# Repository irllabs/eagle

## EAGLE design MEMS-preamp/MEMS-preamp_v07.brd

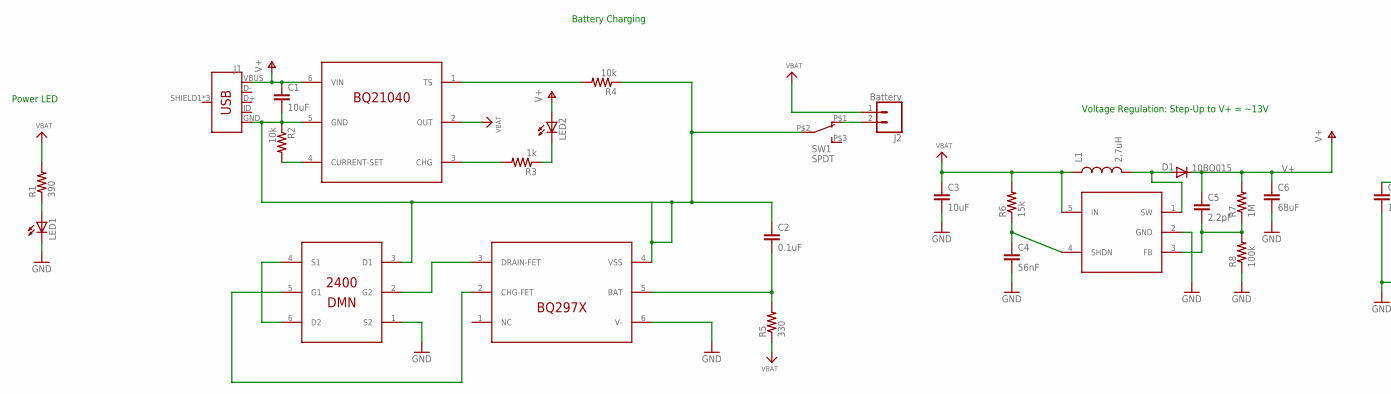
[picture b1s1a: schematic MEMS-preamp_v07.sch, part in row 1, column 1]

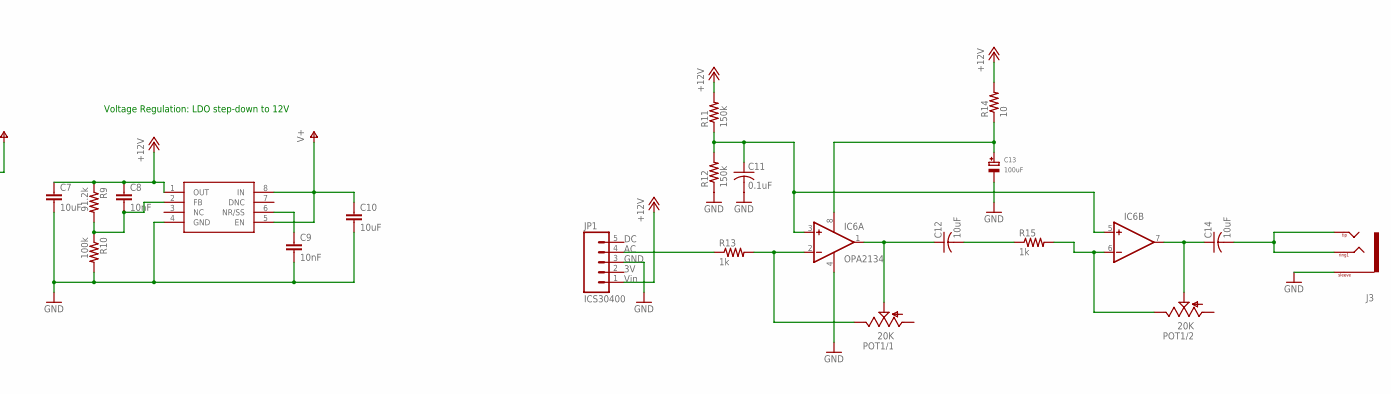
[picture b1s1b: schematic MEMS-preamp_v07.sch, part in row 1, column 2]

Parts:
C1, C3, C7, C10: 10uF; C0603
C2: 0.1uF; C0603
C4: 56nF; C0603
C5: 2.2pF; C0603
C6: 68uF; C1206
C8, C9: 10nF; C0603
C11: 0.1uF; C0805
C12, C14: 10uF; C0805
C13: 100uF; EIA3216-18/A-R
D1: 10BQ015; SMA-DIODE
IC1: DMN2400; SOT-563
IC2: BQ21040; SOT23-6
IC3: BQ297X; WSON-6
IC4: SC4503; SOT23-5
IC5: TPS7A49; MSOP-8
IC6: OPA2134; SO08
J1: USB_MICRO-BREDUCED_PASTE; USB-B-MICRO-SMD_RED_PASTE
J2: Battery; 1X02_LOCK
J3: TRS-1/8"-3.5MM; TRS_SJ-3524-SMT
JP1: ICS30400; 1X05_LOCK
L1: 2.7uH; CR54-KIT
LED1, LED2: LED3MM
POT1: 20K; PTV112
R1: 390; R0603
R2, R4: 10k; R0603
R3, R13, R15: 1k; R0603
R5: 330; R0603
R6: 15k; R0603
R7: 1M; R0603
R8, R10: 100k; R0603
R9: 91.2k; R0603
R11, R12: 150k; R0603
R14: 10; R0603
SW1: SPDT; SWITCH_SPDT_CL-SB-12B

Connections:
+12V: C7.1, C8.1, IC5.1 (OUT), JP1.1, R9.1, R11.2, R14.2
GND: C3.2, C4.2, C6.2, C7.2, C9.2, C10.2, C11.2, C13.-, IC1.1 (S2), IC3.6 (V-), IC5.4 (GND), IC6.4 (V-), J3.1 (SLEEVE), JP1.3, LED1.K (C), R8.1, R10.2, R12.1
GND2: C1.2, C2.1, IC1.3 (D1), IC2.5 (GND), IC3.4 (VSS), J1.GND, R2.1, R4.1, SW1.P$2 (2)
GROU[: IC6.6 (-IN), POT1.2.3 (E), R15.2
unnamed: C13.+, IC6.8 (V+), R14.1
unnamed: LED1.A, R1.1
unnamed: JP1.4, R13.1
unnamed: C12.2, R15.1
unnamed: IC6.2 (-IN), POT1.1.3 (E), R13.2
unnamed: J2.2, SW1.P$1 (1)
unnamed: C14.2, J3.2 (TIP), J3.3 (RING1), J3.4 (TIP)
unnamed: C11.1, IC6.3 (+IN), IC6.5 (+IN), R11.1, R12.2
unnamed: C12.1, IC6.1 (OUT), POT1.1.2 (S)
unnamed: C14.1, IC6.7 (OUT), POT1.2.2 (S)
unnamed: LED2.K (C), R3.1
unnamed: D1.A, IC4.1 (SW), L1.P$2 (2)
unnamed: C4.1, IC4.4 (SHDN), R6.1
unnamed: C5.2, IC4.3 (FB), R7.1, R8.2
unnamed: IC2.3 (CHG), R3.2
unnamed: IC2.1 (TS), R4.2
unnamed: IC2.4 (CURRENT-SET), R2.2
unnamed: C2.2, IC3.5 (BAT), R5.2
unnamed: IC1.4 (S1), IC1.6 (D2)
unnamed: IC1.5 (G1), IC3.2 (CHG-FET)
unnamed: IC1.2 (G2), IC3.3 (DRAIN-FET)
unnamed: C8.2, IC5.2 (FB), R9.2, R10.1
unnamed: C9.1, IC5.6 (NR/SS)
V+: C1.1, C5.1, C6.1, C10.1, D1.C, IC2.6 (VIN), IC5.5 (EN), IC5.8 (IN), J1.VBUS, LED2.A, R7.2
VBAT: C3.1, IC2.2 (OUT), IC4.5 (IN), J2.1, L1.P$1 (1), R1.2, R5.1, R6.2

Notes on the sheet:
Voltage Regulation: Step-Up to V+ = ~13V
Power LED
Voltage Regulation: LDO step-down to 12V
Battery Charging

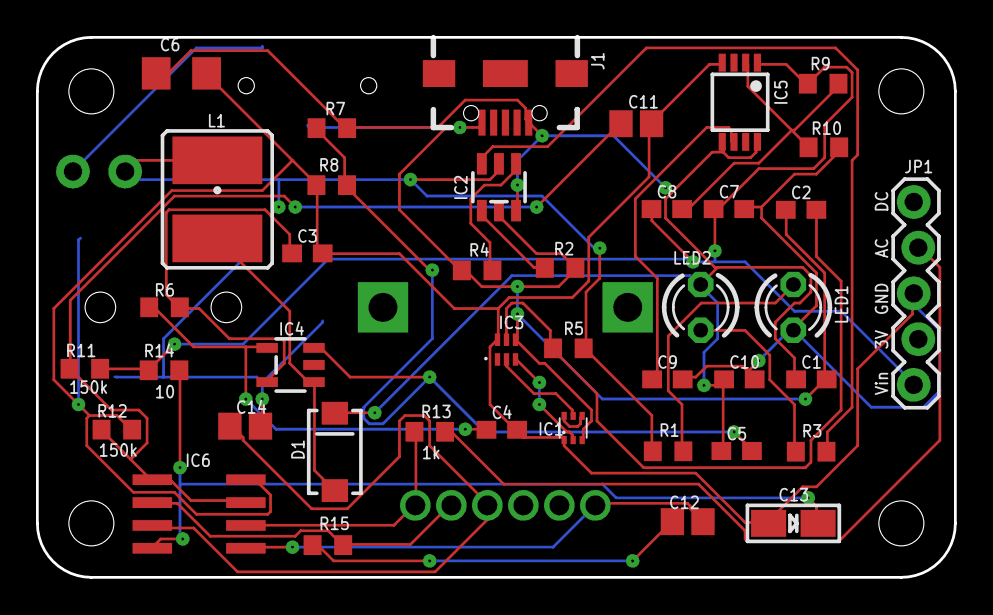
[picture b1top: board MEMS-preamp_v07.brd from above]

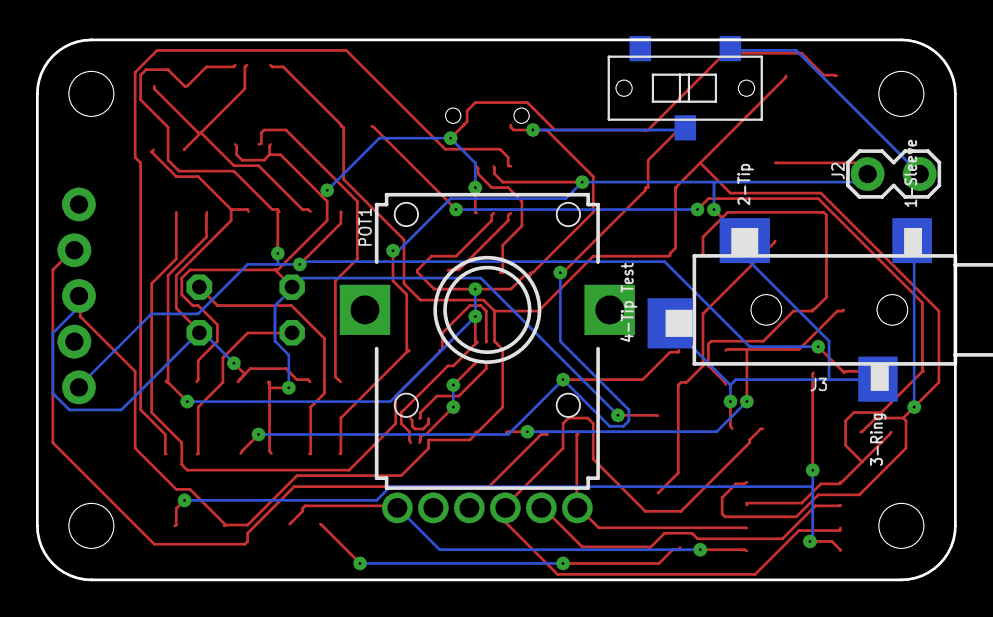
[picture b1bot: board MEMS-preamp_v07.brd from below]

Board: 2 copper layers, 51.0 x 30.0 mm, 45 parts (4 on the bottom side), 29 nets.

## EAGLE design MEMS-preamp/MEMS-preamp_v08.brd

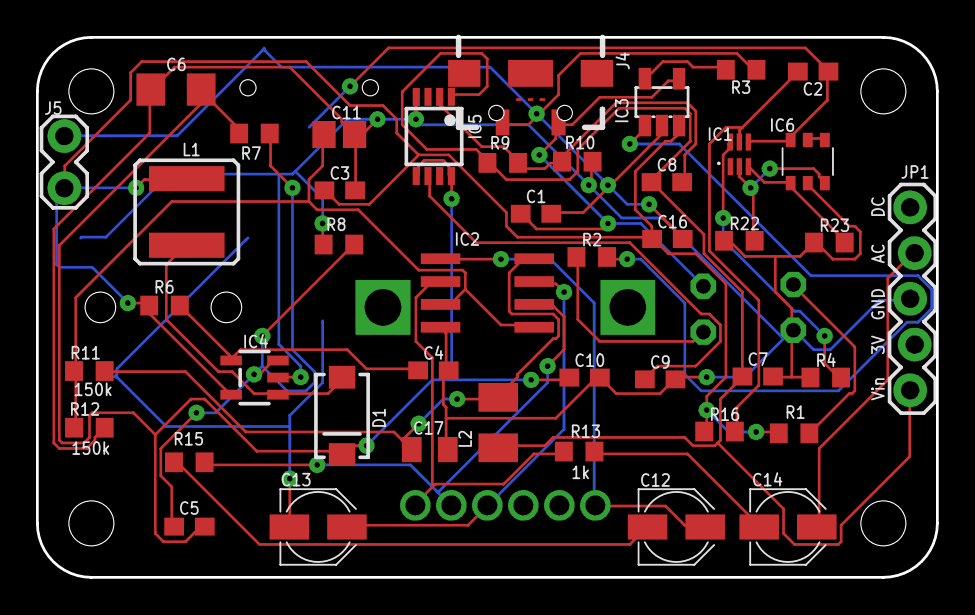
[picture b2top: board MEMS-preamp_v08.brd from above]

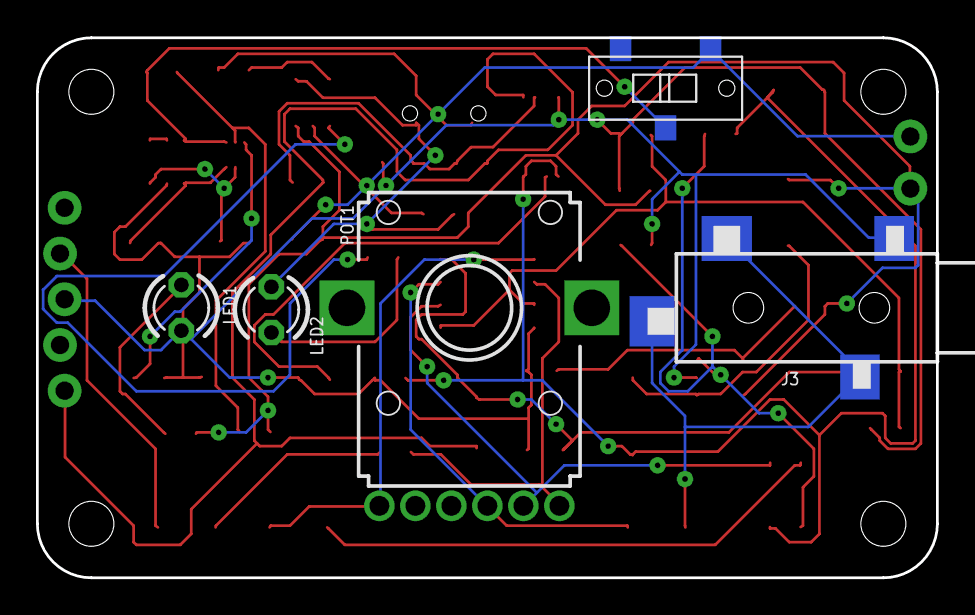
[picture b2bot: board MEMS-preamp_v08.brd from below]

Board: 2 copper layers, 50.0 x 30.0 mm, 49 parts (5 on the bottom side), 31 nets.

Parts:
C1, C16: 4.7uF; C0603
C2: 0.1uF; C0603
C3, C7, C10: 10uF; C0603
C4: 56nF; C0603
C5: 2.2pF; C0603
C6: 68uF; C1206
C8, C9: 10nF; C0603
C11: 0.1uF; C0805
C12, C13, C14: 10uF; PANASONIC_B
C17: 0.1uF; C0805K
D1: 10BQ015; SMA-DIODE
IC1: BQ297X; WSON-6-LONG
IC2: OPA2134UA; SO08
IC3: MCP73831; SOT-23-5
IC4: SC4503; SOT23-5
IC5: TPS7A49; MSOP-8
IC6: QS6K1; SOT457R_PHILIPS
J3: TRS-1/8"-3.5MM; TRS_SJ-3524-SMT
J4: USB-B-MICRO-SMD_RED_PASTE
J5: Battery; 1X02_LOCK
JP1: ICS40300; 1X05_LOCK
L1: 2.7uH; CR54
L2: 100uH/500mA; L3225M
LED1: LED3MM
LED2: Charge; LED3MM
POT1: 20K; PTV112
R1: 390; R0603
R2: 470; R0603
R3: 5k; R0603
R4: 2.2k; R0603
R6: 15k; R0603
R7: 1M; R0603
R8, R9: 100k; R0603
R10: 11k; R0603
R11, R12: 150k; R0603
R13, R15: 1k; R0603
R16: 330; R0603
R22, R23: 10M; R0603
SW3: SPDT; SWITCH_SPDT_CL-SB-12B

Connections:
+5V: C1.1, IC3.4, J4.VBUS, LED2.A
+12V: C7.1, C8.1, IC5.1, JP1.1, L2.1, R9.1
BATGND: C2.1, IC1.4, IC6.6, SW3.P$2
GND: C3.2, C4.2, C6.2, C7.2, C9.2, C10.2, C11.2, C17.2, IC2.4, IC4.2, IC5.4, IC6.2, J3.1, JP1.3, LED1.K, R4.1, R8.1, R10.2, R12.1, R22.1, R23.1
unnamed: LED1.A, R1.1
unnamed: C14.+, JP1.4
unnamed: C12.-, R15.1
unnamed: IC2.2, POT1.1.3, R13.2
unnamed: IC3.5, R3.2
unnamed: C13.-, J3.2, J3.3, J3.4
unnamed: C11.1, IC2.3, IC2.5, R11.1, R12.2
unnamed: C12.+, IC2.1, POT1.1.2
unnamed: C13.+, IC2.7, POT1.2.2
unnamed: IC6.4, IC6.5
unnamed: D1.A, IC4.1, L1.P$2
unnamed: C4.1, IC4.4, R6.1
unnamed: C5.2, IC4.3, R7.1, R8.2
unnamed: C17.1, IC2.8, L2.2, R11.2
unnamed: IC2.6, POT1.2.3, R15.2
unnamed: LED2.K, R2.1
unnamed: C14.-, R13.1
unnamed: IC3.1, R2.2
unnamed: IC1.3, IC6.1, R23.2
unnamed: IC1.2, IC6.3, R22.2
unnamed: IC1.6, R4.2
unnamed: C2.2, IC1.5, R16.2
unnamed: C8.2, IC5.2, R9.2, R10.1
unnamed: C9.1, IC5.6
USBGND: C1.2, C16.2, IC3.2, J4.GND, J5.2, R3.1, SW3.P$1
V+: C5.1, C6.1, C10.1, D1.C, IC5.5, IC5.8, R7.2
VBAT: C3.1, C16.1, IC3.3, IC4.5, J5.1, L1.P$1, R1.2, R6.2, R16.1

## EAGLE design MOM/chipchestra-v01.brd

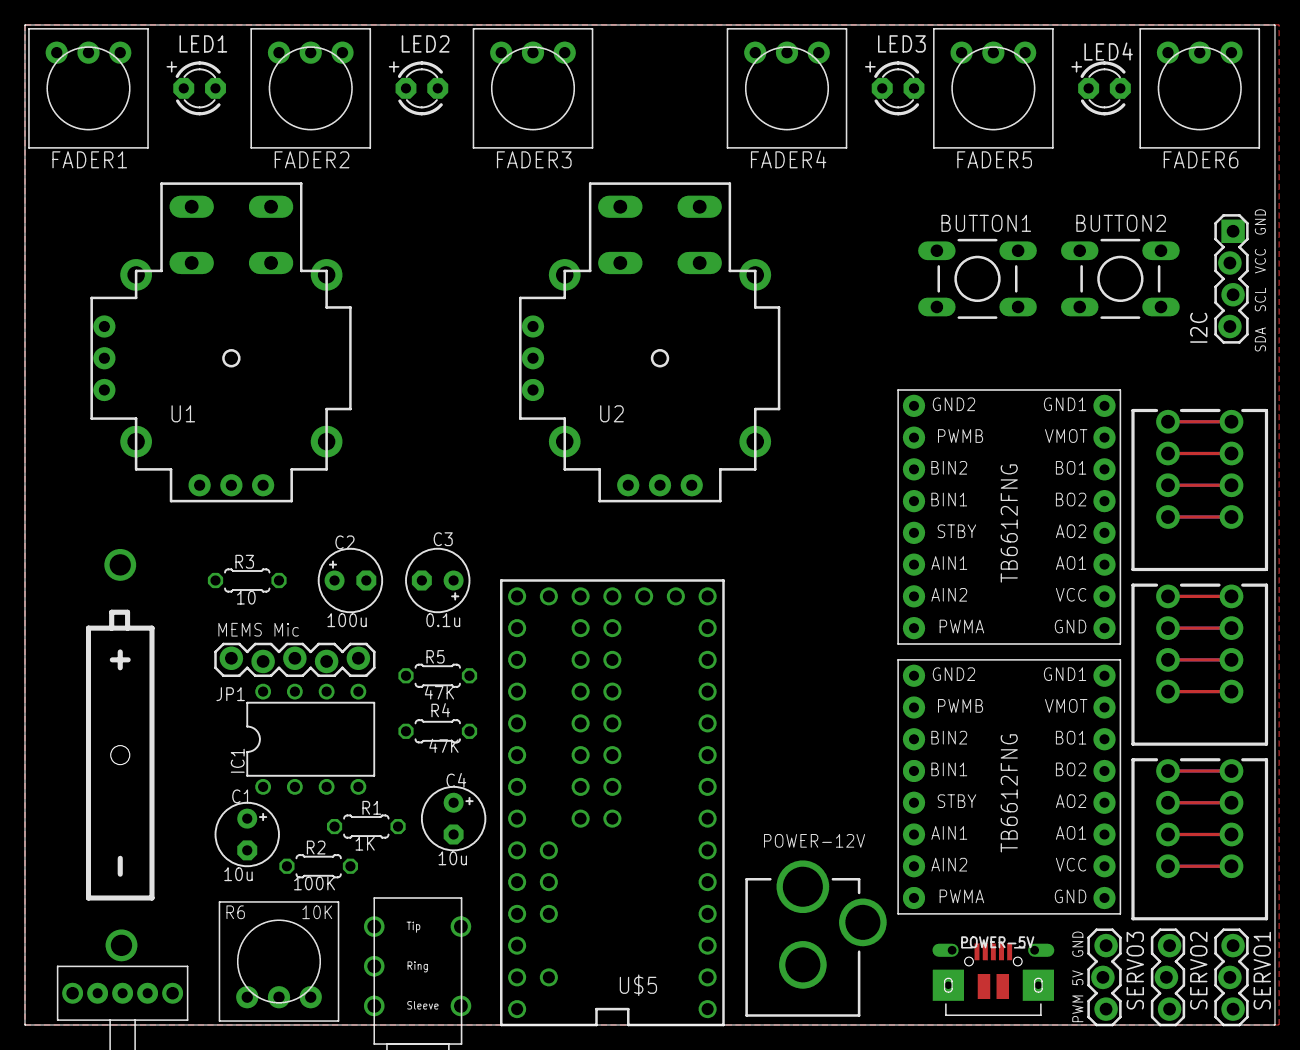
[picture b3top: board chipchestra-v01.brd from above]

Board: 2 copper layers, 100.0 x 80.0 mm, 41 parts (0 on the bottom side), 61 nets, no tracks yet.

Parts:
BAT1: BATTERY-A23
BUTTON1, BUTTON2: DTS-6
C1, C4: 10u; E2,5-5
C2: 100u; E2,5-5
C3: 0.1u; E2,5-5
FADER1, FADER2, FADER3, FADER4, FADER5, FADER6: TRIM-3386
I2C: 1X04_LOCK
IC1: OPA2134PA; DIL08
JP1: MEMS Mic; 1X05_LOCK
LED1, LED2, LED3, LED4: LED3MM
MOTORS1, MOTORS2: SPRINGTERMINAL-2.54MM-4
ON/OFF: labl; SPDT-SWITCH
POWER-5V: 4UCONN_20329
POWER-12V: DCJACK_2MM_PTH
R1: 1K; 0204/5
R2: 100K; 0204/5
R3: 10; 0204/5
R4, R5: 47K; 0204/5
R6: 10K; TRIM-3386
SERVO1, SERVO2, SERVO3: 1X03_LOCK
TO-AUDIO-IO: 1/8"-F-STEREO-PCB
TOUCH: SPRINGTERMINAL-2.54MM-4
U1, U2: JOYSTICKPTH; JOYSTICK
U$5: TEENSY_3.1-3.2_ALL_PINS&PADS; TEENSY_3.0-3.2_ALL_PINS_&_PADS
U$6, U$7: POLOLU_TB6612FNG

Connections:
+3V3: I2C.1, JP1.2, U$5.3.3V, U$5.3.3V1, U$5.3.3V2
+5V: FADER1.1, FADER2.1, FADER3.1, FADER4.1, FADER5.1, FADER6.1, U1.H1, U1.V1, U2.H1, U2.V1, U$5.VUSB, U$6.STBY, U$6.VCC, U$7.STBY, U$7.VCC
ANALOG1: FADER1.2, U$5.14/A0
ANALOG2: FADER2.2, U$5.23/A9
ANALOG3: FADER3.2, U$5.31
ANALOG4: FADER4.2, U$5.A10
ANALOG5: FADER5.2, U$5.A11
ANALOG6: FADER6.2, U$5.A12
BUTTON1: BUTTON1.3, U$5.A13
BUTTON2: BUTTON2.3, U$5.RESET/DAC
GND: BUTTON1.1, BUTTON2.1, FADER1.3, FADER2.3, FADER3.3, FADER4.3, FADER5.3, FADER6.3, I2C.2, LED1.K, LED2.K, LED3.K, LED4.K, POWER-5V.BASE@1, POWER-5V.BASE@2, POWER-5V.GND, POWER-5V.SPRT@1, POWER-5V.SPRT@2, POWER-5V.SPRT@3, POWER-5V.SPRT@4, SERVO1.1, SERVO2.1, SERVO3.1, U1.B2A, U1.H3, U1.V3, U2.B2A, U2.H3, U2.V3, U$5.GND, U$5.GND1, U$5.GND2, U$6.GND, U$6.GND2, U$7.GND, U$7.GND2
GND_MIC: C2.-, C3.-, IC1.4, JP1.3, R4.1, R6.1, TO-AUDIO-IO.TIP1, TO-AUDIO-IO.TIP2
GND_MOT: POWER-12V.GND, U$6.GND1, U$7.GND1
I2C_SCL0: I2C.3, U$5.19/A5
I2C_SDA0: I2C.4, U$5.18/A4
JOYB1: U1.B1A, U2.B1A, U$5.24
JOYH1: U1.H2, U2.H2, U$5.27
JOYV1: U1.V2, U2.V2, U$5.26
LED1: LED1.A, U$5.5
LED2: LED2.A, U$5.6
LED3: LED3.A, U$5.20/A6
LED4: LED4.A, U$5.21/A7
MOT_AIN1_1: U$5.0, U$7.AIN1
MOT_AIN1_2: U$5.8, U$6.AIN1
MOT_AIN2_1: U$5.1, U$7.AIN2
MOT_AIN2_2: U$5.11, U$6.AIN2
MOT_BIN1_1: U$5.7, U$7.BIN1
MOT_BIN1_2: U$5.13, U$6.BIN1
MOT_BIN2_1: U$5.2, U$7.BIN2
MOT_BIN2_2: U$5.12, U$6.BIN2
MOT_PWMA_1: U$5.3, U$7.PWMA
MOT_PWMA_2: U$5.9, U$6.PWMA
MOT_PWMB_1: U$5.4, U$7.PWMB
MOT_PWMB_2: U$5.10, U$6.PWMB
unnamed: C2.+, IC1.8, R3.1
unnamed: BAT1.GND@1, ON/OFF.1
unnamed: C4.+, JP1.4
unnamed: C4.-, R1.1
unnamed: IC1.2, R1.2, R2.1
unnamed: C1.-, R6.3
unnamed: R6.2, TO-AUDIO-IO.SLEEVE1, TO-AUDIO-IO.SLEEVE2
unnamed: C3.+, IC1.3, R4.2, R5.1
unnamed: C1.+, IC1.1, R2.2
unnamed: MOTORS1.P$1, U$7.BO1
unnamed: MOTORS1.P$2, U$7.BO2
unnamed: MOTORS1.P$3, U$7.AO2
unnamed: MOTORS1.P$4, U$7.AO1
unnamed: MOTORS2.P$1, U$6.BO1
unnamed: MOTORS2.P$2, U$6.BO2
unnamed: MOTORS2.P$3, U$6.AO2
unnamed: MOTORS2.P$4, U$6.AO1
SERVO1: SERVO3.3, U$5.22/A8
SERVO2: SERVO2.3, U$5.25
SERVO3: SERVO1.3, U$5.32
TOUCH1: TOUCH.P$1, U$5.15/A1
TOUCH2: TOUCH.P$2, U$5.16/A2
TOUCH3: TOUCH.P$3, U$5.17/A3
TOUCH4: TOUCH.P$4, U$5.33
VBAT: SERVO1.2, SERVO2.2, SERVO3.2
VMIC: BAT1.PWR@1, R3.2, R5.2
VMOT: POWER-12V.PWR, U$6.VMOT

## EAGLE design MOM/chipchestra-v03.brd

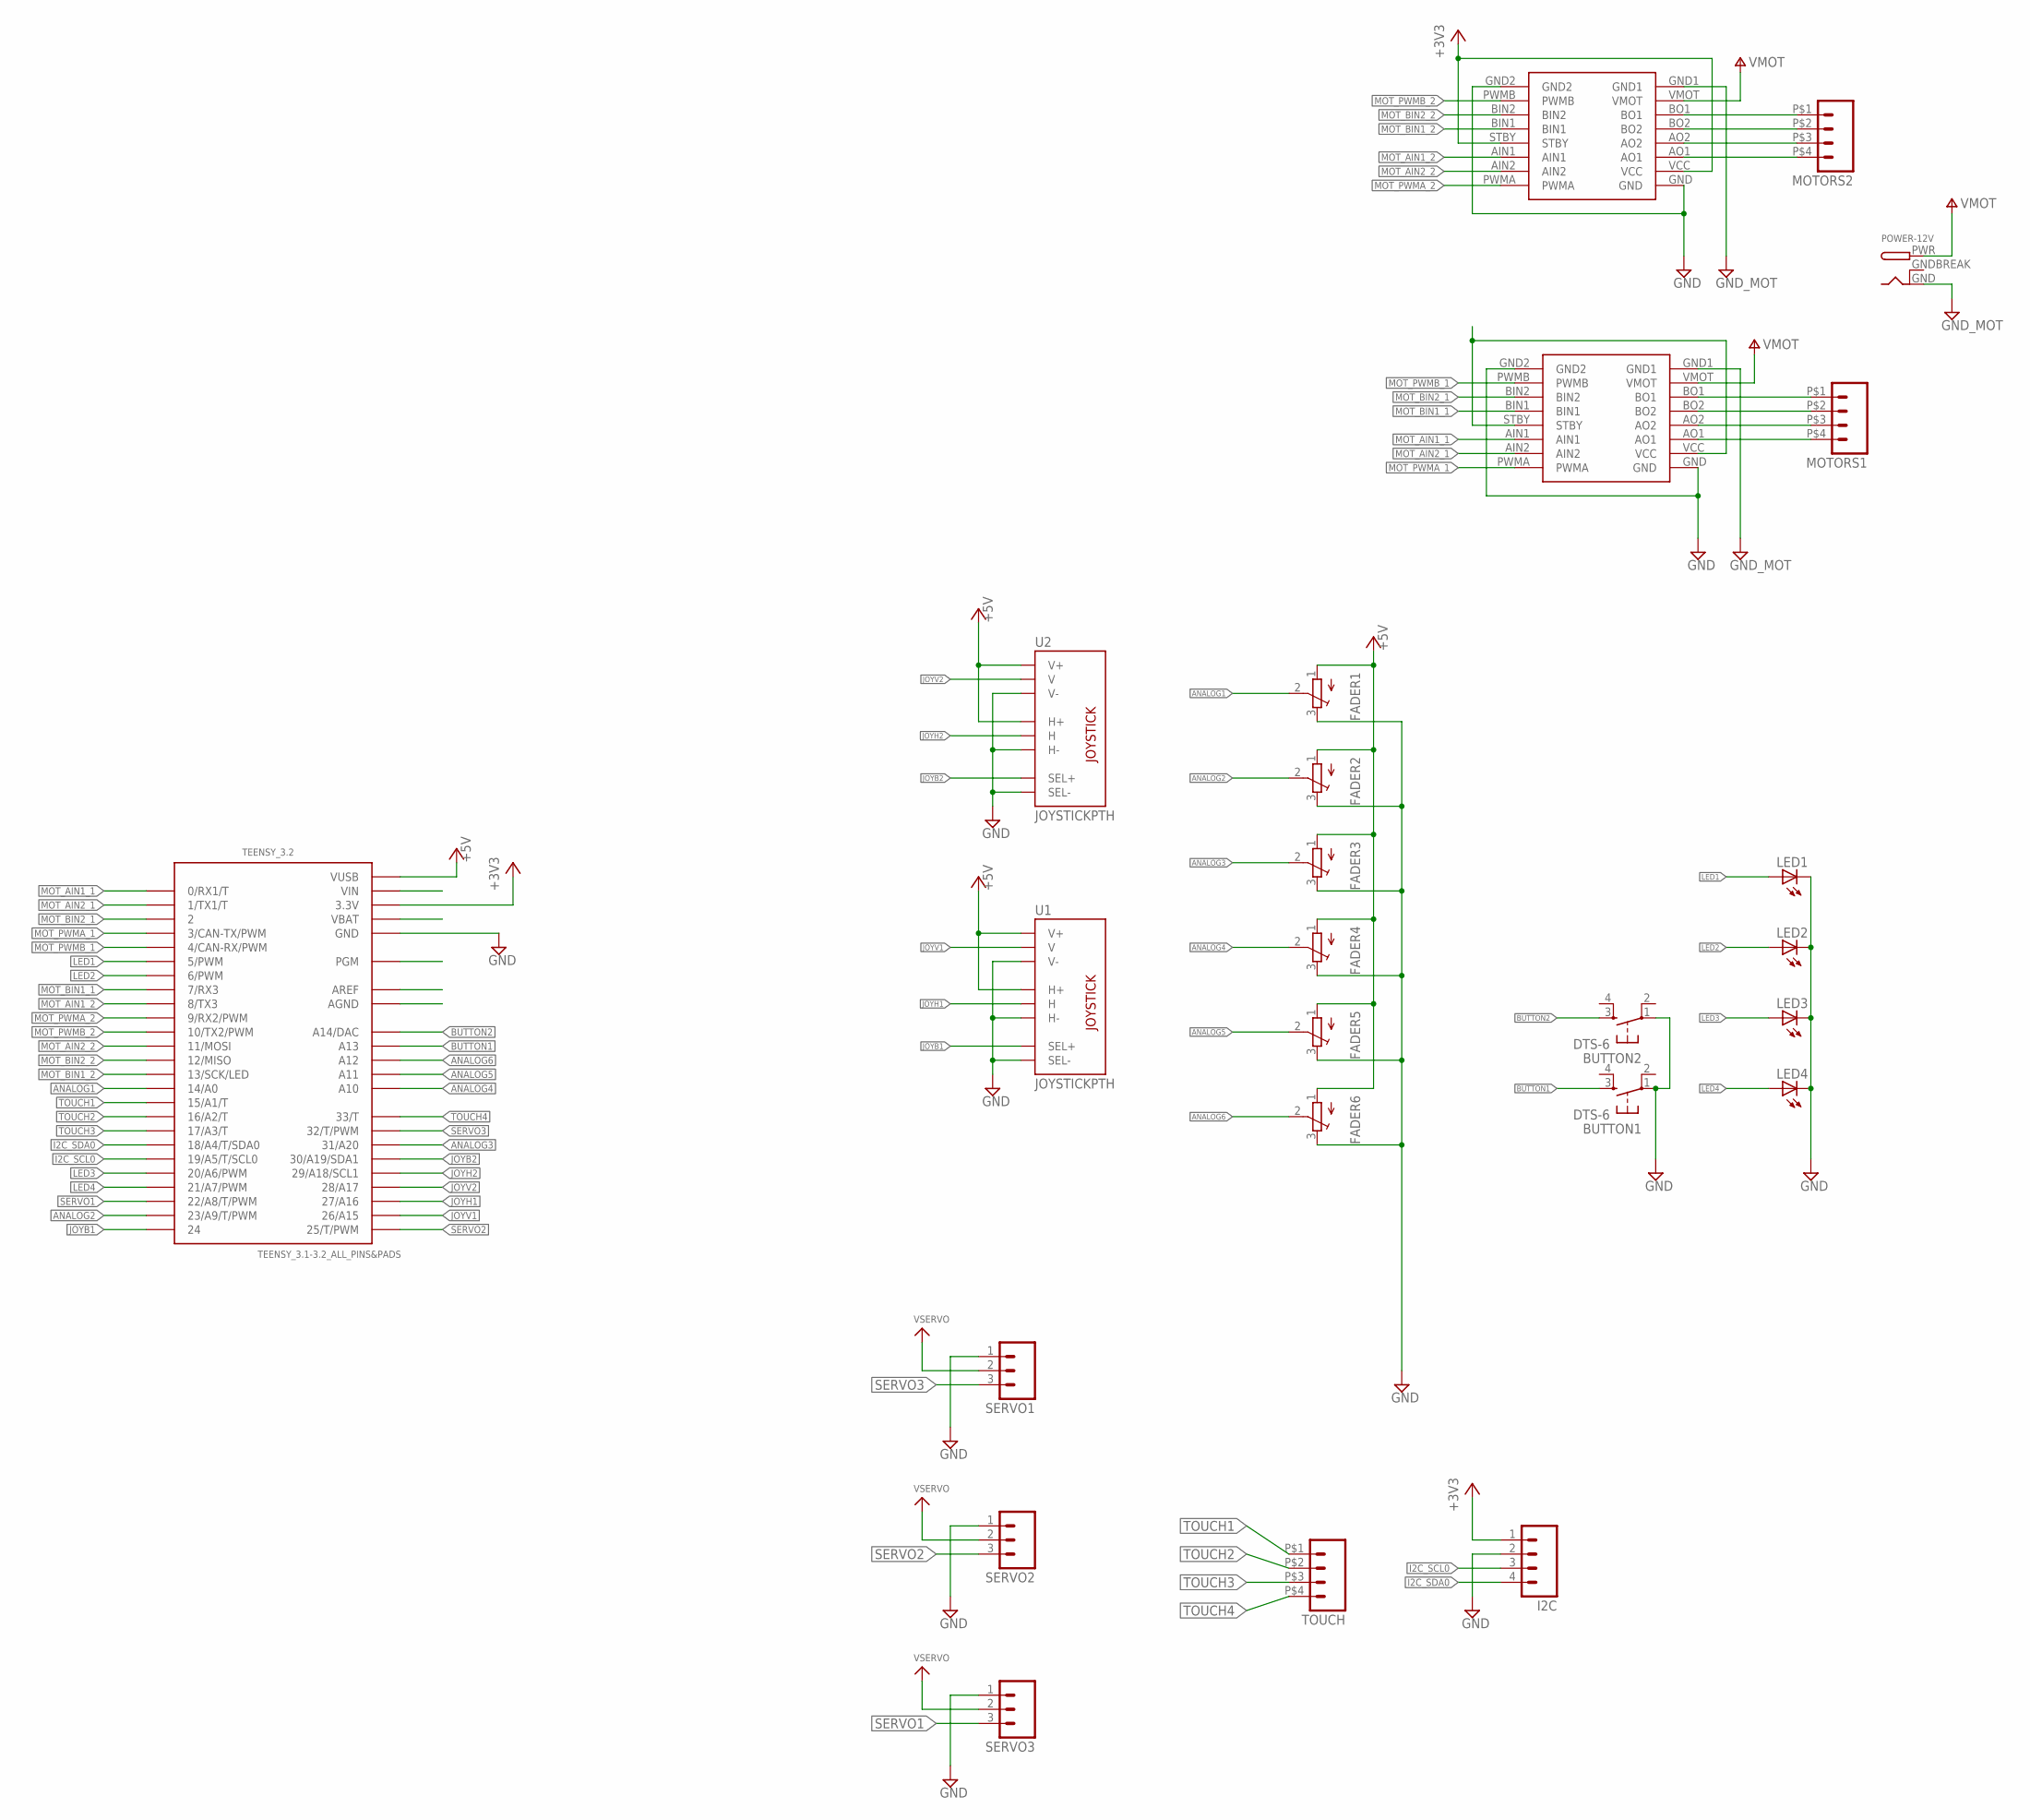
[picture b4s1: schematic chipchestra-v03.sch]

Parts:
BUTTON1, BUTTON2: DTS-6
FADER1, FADER2, FADER3, FADER4, FADER5, FADER6: TRIMPOT3386; TRIM-3386
I2C: M04LOCK; 1X04_LOCK
LED1, LED2, LED3, LED4: LED3MM
MOTORS1, MOTORS2: M04; SPRINGTERMINAL-2.54MM-4
POWER-12V: DCBARRELPTH; DCJACK_2MM_PTH
SERVO1, SERVO2, SERVO3: M03LOCK; 1X03_LOCK
TEENSY_3.2: TEENSY_3.1-3.2_ALL_PINS&PADS; TEENSY_3.0-3.2_ALL_PINS_&_PADS
TOUCH: M04; SPRINGTERMINAL-2.54MM-4
U1, U2: JOYSTICKPTH; JOYSTICK
U$6, U$7: POLOLU_TB6612FNG

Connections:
+3V3: I2C.1, TEENSY_3.2.3.3V, TEENSY_3.2.3.3V1 (3.3V), TEENSY_3.2.3.3V2 (3.3V), U$6.STBY, U$6.VCC
+5V: FADER1.1 (A), FADER2.1 (A), FADER3.1 (A), FADER4.1 (A), FADER5.1 (A), FADER6.1 (A), TEENSY_3.2.VUSB, U1.H1 (H+), U1.V1 (V+), U2.H1 (H+), U2.V1 (V+)
ANALOG1: FADER1.2 (S), TEENSY_3.2.14/A0
ANALOG2: FADER2.2 (S), TEENSY_3.2.23/A9 (23/A9/T/PWM)
ANALOG3: FADER3.2 (S), TEENSY_3.2.31 (31/A20)
ANALOG4: FADER4.2 (S), TEENSY_3.2.A10
ANALOG5: FADER5.2 (S), TEENSY_3.2.A11
ANALOG6: FADER6.2 (S), TEENSY_3.2.A12
BUTTON1: BUTTON1.3, TEENSY_3.2.A13
BUTTON2: BUTTON2.3, TEENSY_3.2.RESET/DAC (A14/DAC)
GND: BUTTON1.1, BUTTON2.1, FADER1.3 (E), FADER2.3 (E), FADER3.3 (E), FADER4.3 (E), FADER5.3 (E), FADER6.3 (E), I2C.2, LED1.K (C), LED2.K (C), LED3.K (C), LED4.K (C), SERVO1.1, SERVO2.1, SERVO3.1, TEENSY_3.2.GND, TEENSY_3.2.GND1 (GND), TEENSY_3.2.GND2 (GND), U1.B2A (SEL-), U1.H3 (H-), U1.V3 (V-), U2.B2A (SEL-), U2.H3 (H-), U2.V3 (V-), U$6.GND, U$6.GND2, U$7.GND, U$7.GND2
GNDBREAK: POWER-12V.GNDBREAK
GND_MOT: POWER-12V.GND, U$6.GND1, U$7.GND1
I2C_SCL0: I2C.3, TEENSY_3.2.19/A5 (19/A5/T/SCL0)
I2C_SDA0: I2C.4, TEENSY_3.2.18/A4 (18/A4/T/SDA0)
JOYB1: TEENSY_3.2.24, U1.B1A (SEL+)
JOYB2: TEENSY_3.2.30 (30/A19/SDA1), U2.B1A (SEL+)
JOYH1: TEENSY_3.2.27 (27/A16), U1.H2 (H)
JOYH2: TEENSY_3.2.29 (29/A18/SCL1), U2.H2 (H)
JOYV1: TEENSY_3.2.26 (26/A15), U1.V2 (V)
JOYV2: TEENSY_3.2.28 (28/A17), U2.V2 (V)
LED1: LED1.A, TEENSY_3.2.5 (5/PWM)
LED2: LED2.A, TEENSY_3.2.6 (6/PWM)
LED3: LED3.A, TEENSY_3.2.20/A6 (20/A6/PWM)
LED4: LED4.A, TEENSY_3.2.21/A7 (21/A7/PWM)
MOT_AIN1_1: TEENSY_3.2.0 (0/RX1/T), U$7.AIN1
MOT_AIN1_2: TEENSY_3.2.8 (8/TX3), U$6.AIN1
MOT_AIN2_1: TEENSY_3.2.1 (1/TX1/T), U$7.AIN2
MOT_AIN2_2: TEENSY_3.2.11 (11/MOSI), U$6.AIN2
MOT_BIN1_1: TEENSY_3.2.7 (7/RX3), U$7.BIN1
MOT_BIN1_2: TEENSY_3.2.13 (13/SCK/LED), U$6.BIN1
MOT_BIN2_1: TEENSY_3.2.2, U$7.BIN2
MOT_BIN2_2: TEENSY_3.2.12 (12/MISO), U$6.BIN2
MOT_PWMA_1: TEENSY_3.2.3 (3/CAN-TX/PWM), U$7.PWMA
MOT_PWMA_2: TEENSY_3.2.9 (9/RX2/PWM), U$6.PWMA
MOT_PWMB_1: TEENSY_3.2.4 (4/CAN-RX/PWM), U$7.PWMB
MOT_PWMB_2: TEENSY_3.2.10 (10/TX2/PWM), U$6.PWMB
unnamed: U$7.STBY, U$7.VCC
unnamed: MOTORS1.P$1 (1), U$7.BO1
unnamed: MOTORS1.P$2 (2), U$7.BO2
unnamed: MOTORS1.P$3 (3), U$7.AO2
unnamed: MOTORS1.P$4 (4), U$7.AO1
unnamed: MOTORS2.P$1 (1), U$6.BO1
unnamed: MOTORS2.P$2 (2), U$6.BO2
unnamed: MOTORS2.P$3 (3), U$6.AO2
unnamed: MOTORS2.P$4 (4), U$6.AO1
SERVO1: SERVO3.3, TEENSY_3.2.22/A8 (22/A8/T/PWM)
SERVO2: SERVO2.3, TEENSY_3.2.25 (25/T/PWM)
SERVO3: SERVO1.3, TEENSY_3.2.32 (32/T/PWM)
TOUCH1: TEENSY_3.2.15/A1 (15/A1/T), TOUCH.P$1 (1)
TOUCH2: TEENSY_3.2.16/A2 (16/A2/T), TOUCH.P$2 (2)
TOUCH3: TEENSY_3.2.17/A3 (17/A3/T), TOUCH.P$3 (3)
TOUCH4: TEENSY_3.2.33 (33/T), TOUCH.P$4 (4)
VBAT: SERVO1.2, SERVO2.2, SERVO3.2
VMOT: POWER-12V.PWR, U$6.VMOT, U$7.VMOT

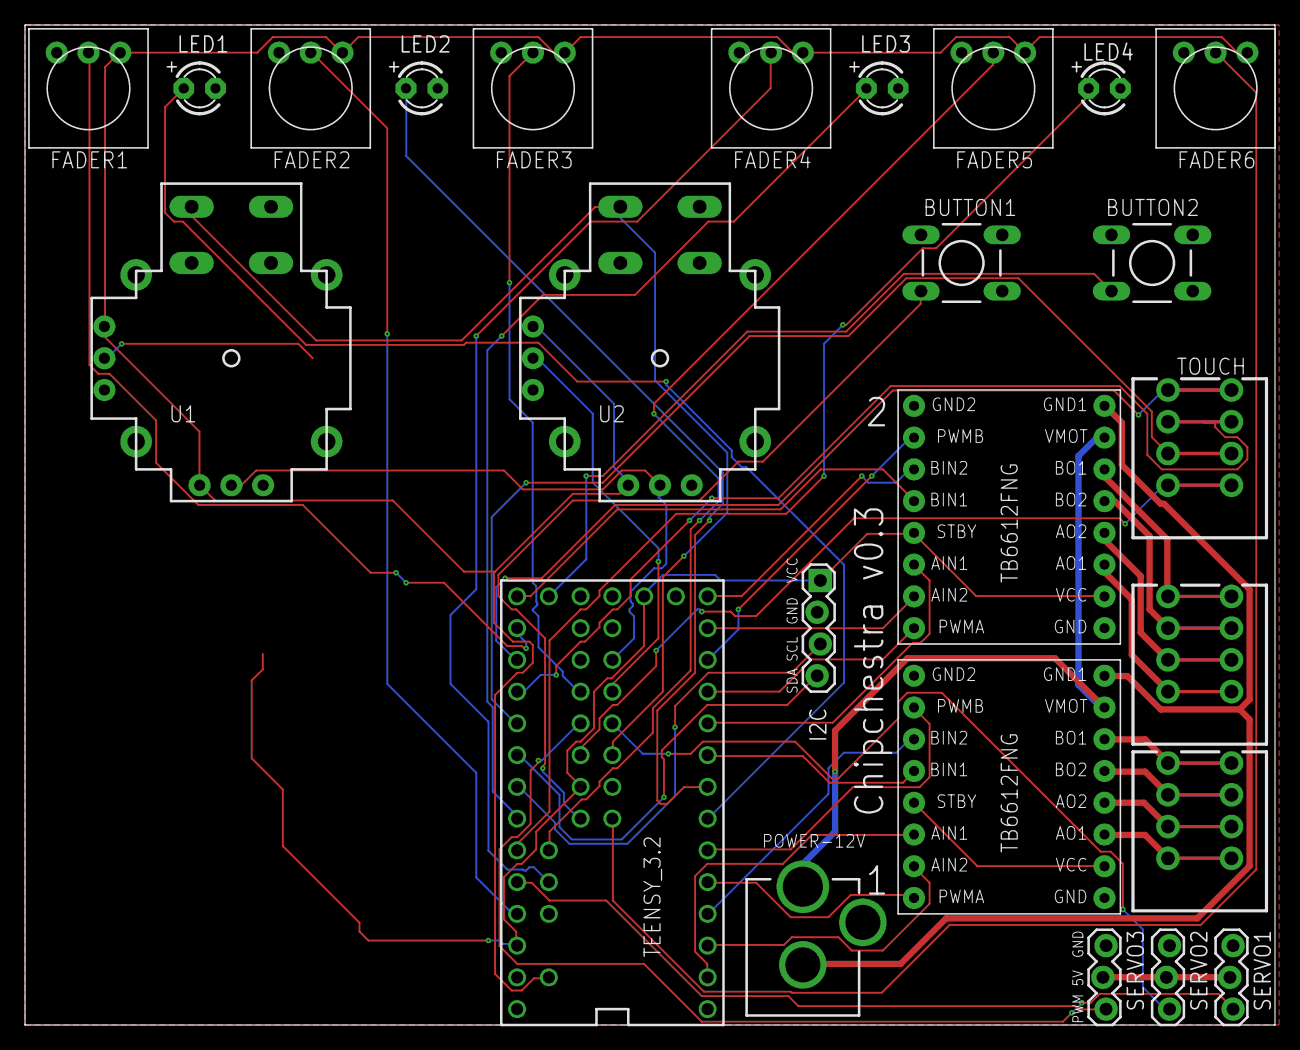
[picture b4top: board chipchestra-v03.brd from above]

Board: 2 copper layers, 100.0 x 80.0 mm, 25 parts (0 on the bottom side), 54 nets.

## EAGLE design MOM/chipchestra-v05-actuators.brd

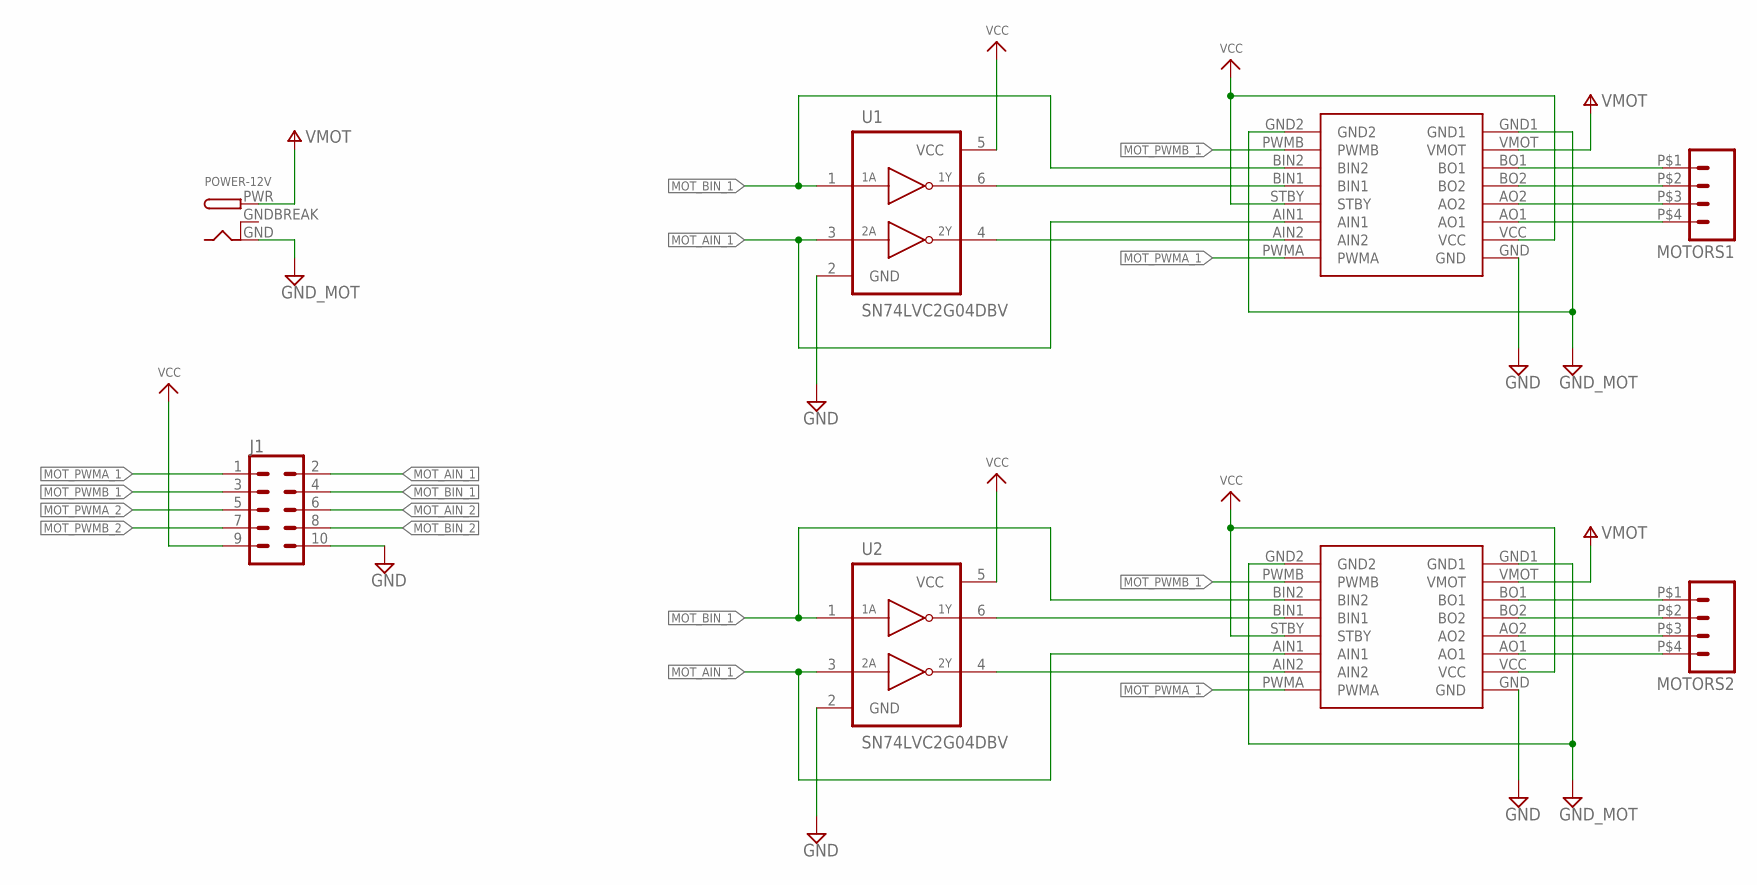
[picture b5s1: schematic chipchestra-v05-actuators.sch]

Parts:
J1: CONN_05X2SHD_LOCK; 2X5-SHROUDED_LOCK
MOTORS1, MOTORS2: M04; SPRINGTERMINAL-2.54MM-4
POWER-12V: DCBARRELPTH; DCJACK_2MM_PTH
U1, U2: SN74LVC2G04DBV; SOT23-6
U$1, U$7: POLOLU_TB6612FNG

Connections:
GND: J1.10, U1.2 (GND), U2.2 (GND), U$1.GND, U$7.GND
GNDBREAK: POWER-12V.GNDBREAK
GND_MOT: POWER-12V.GND, U$1.GND1, U$1.GND2, U$7.GND1, U$7.GND2
MOT_AIN_1: J1.2, U1.3 (2A), U2.3 (2A), U$1.AIN1, U$7.AIN1
MOT_AIN_2: J1.6
MOT_BIN_1: J1.4, U1.1 (1A), U2.1 (1A), U$1.BIN2, U$7.BIN2
MOT_BIN_2: J1.8
MOT_PWMA_1: J1.1, U$1.PWMA, U$7.PWMA
MOT_PWMA_2: J1.5
MOT_PWMB_1: J1.3, U$1.PWMB, U$7.PWMB
MOT_PWMB_2: J1.7
unnamed: MOTORS2.P$1 (1), U$1.BO1
unnamed: MOTORS2.P$2 (2), U$1.BO2
unnamed: MOTORS2.P$3 (3), U$1.AO2
unnamed: MOTORS2.P$4 (4), U$1.AO1
unnamed: U1.6 (1Y), U$7.BIN1
unnamed: U1.4 (2Y), U$7.AIN2
unnamed: U2.6 (1Y), U$1.BIN1
unnamed: U2.4 (2Y), U$1.AIN2
unnamed: MOTORS1.P$1 (1), U$7.BO1
unnamed: MOTORS1.P$2 (2), U$7.BO2
unnamed: MOTORS1.P$3 (3), U$7.AO2
unnamed: MOTORS1.P$4 (4), U$7.AO1
VCC: J1.9, U1.5 (VCC), U2.5 (VCC), U$1.STBY, U$1.VCC, U$7.STBY, U$7.VCC
VMOT: POWER-12V.PWR, U$1.VMOT, U$7.VMOT

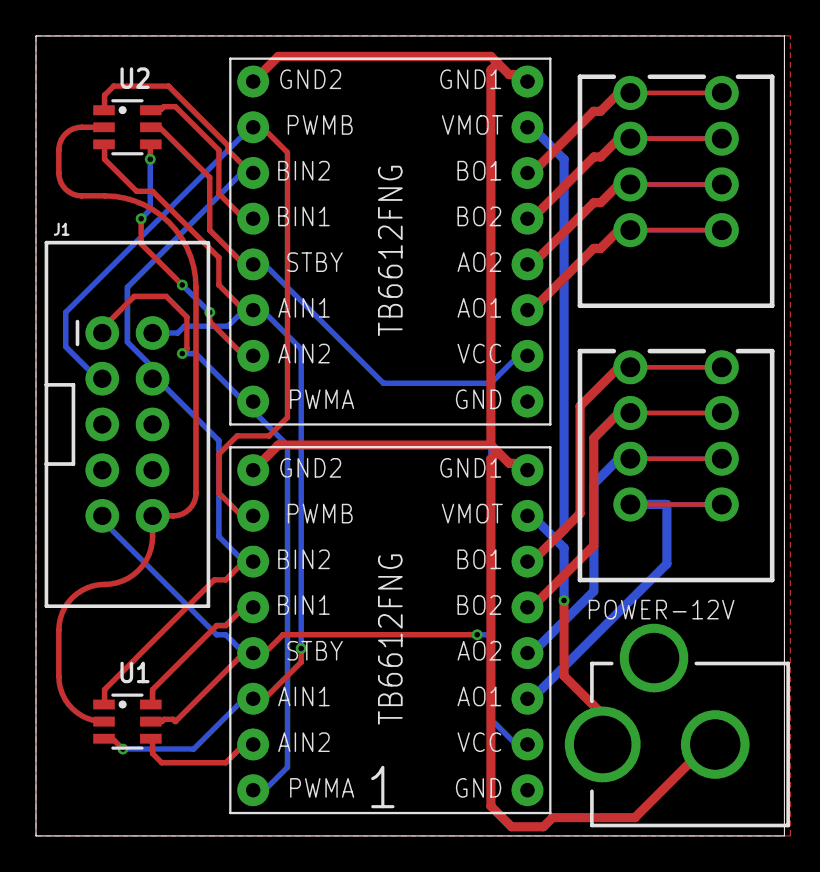
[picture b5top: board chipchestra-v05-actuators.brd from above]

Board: 2 copper layers, 41.6 x 44.4 mm, 8 parts (0 on the bottom side), 20 nets.

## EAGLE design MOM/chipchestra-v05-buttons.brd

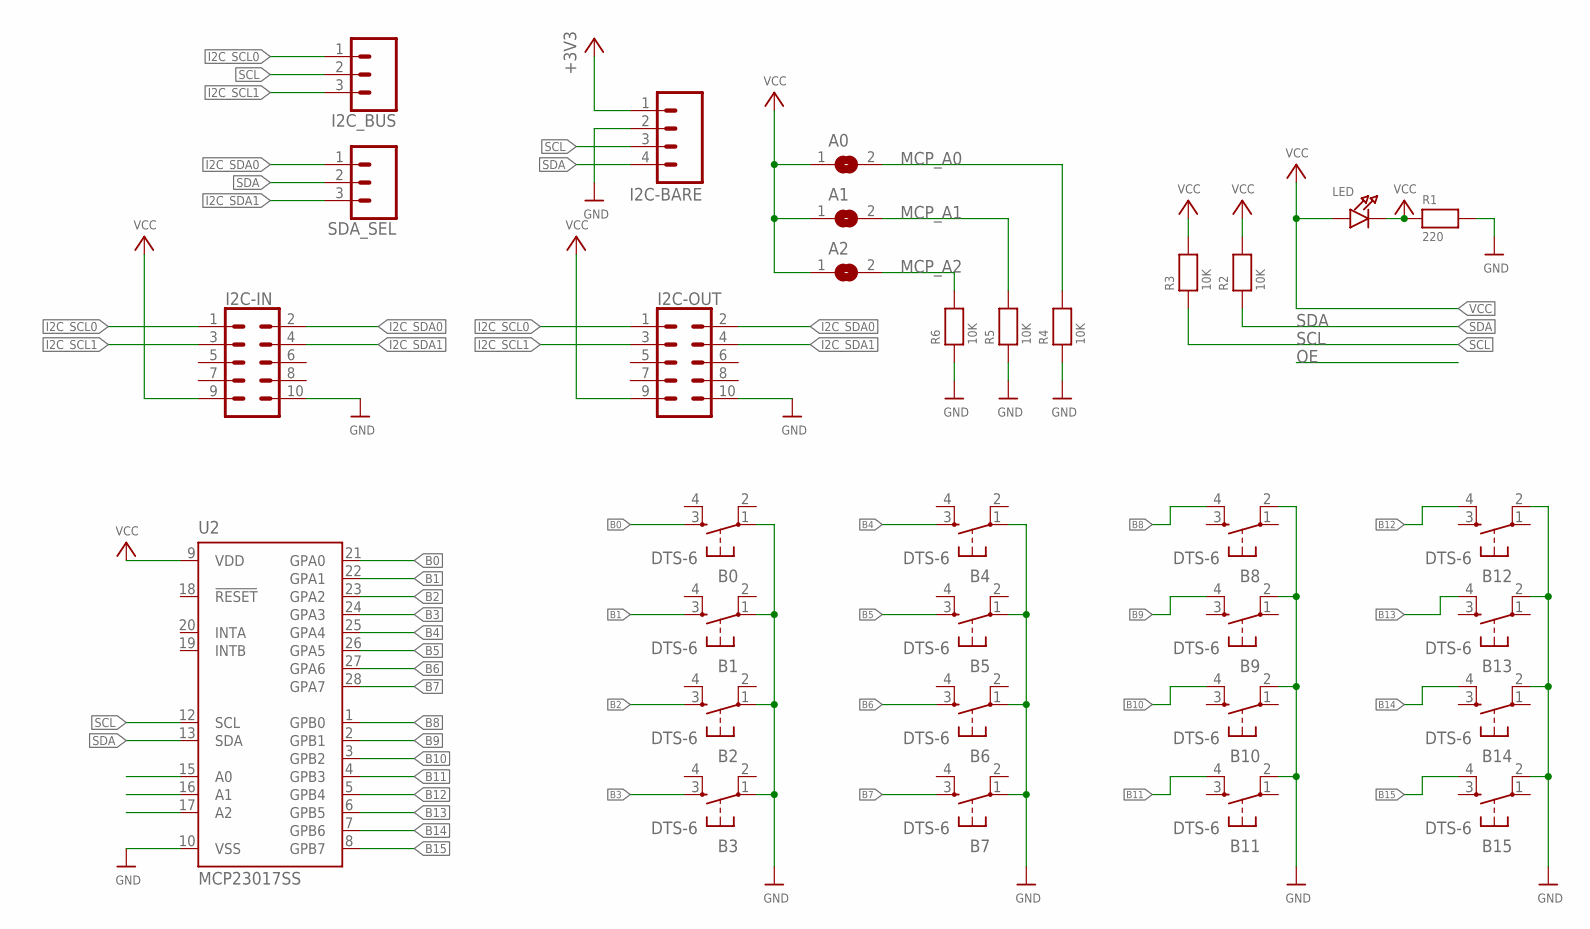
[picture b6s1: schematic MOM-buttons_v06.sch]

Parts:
A0, A1, A2: SOLDERJUMPERREFLOW_NOPASTE; SOLDERJUMPER_REFLOW_NOPASTE
B0, B1, B2, B3, B4, B5, B6, B7, B8, B9, B10, B11, B12, B13, B14, B15: DTS-6
I2C-BARE: M04LOCK; 1X04_LOCK
I2C-IN, I2C-OUT: CONN_05X2SHD_LOCK; 2X5-SHROUDED_LOCK
I2C_BUS: CONN_03LOCK; 1X03_LOCK
LED: LED0805; CHIPLED_0805
R1: 220; 0805
R2, R3, R4, R5, R6: 10K; 0805
SDA_SEL: CONN_03LOCK; 1X03_LOCK
U2: MCP23017SS; SSOP28

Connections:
+3V3: I2C-BARE.1
B0: B0.3, U2.21 (GPA0)
B1: B1.3, U2.22 (GPA1)
B2: B2.3, U2.23 (GPA2)
B3: B3.3, U2.24 (GPA3)
B4: B4.3, U2.25 (GPA4)
B5: B5.3, U2.26 (GPA5)
B6: B6.3, U2.27 (GPA6)
B7: B7.3, U2.28 (GPA7)
B8: B8.4, U2.1 (GPB0)
B9: B9.4, U2.2 (GPB1)
B10: B10.4, U2.3 (GPB2)
B11: B11.4, U2.4 (GPB3)
B12: B12.4, U2.5 (GPB4)
B13: B13.4, U2.6 (GPB5)
B14: B14.4, U2.7 (GPB6)
B15: B15.4, U2.8 (GPB7)
GND: B0.1, B1.1, B2.1, B3.1, B4.1, B5.1, B6.1, B7.1, B8.2, B9.2, B10.2, B11.2, B12.2, B13.2, B14.2, B15.2, I2C-BARE.2, I2C-IN.10, I2C-OUT.10, R1.2, R4.1, R5.1, R6.1, U2.10 (VSS)
I2C_SCL0: I2C-IN.1, I2C-OUT.1, I2C_BUS.1
I2C_SCL1: I2C-IN.3, I2C-OUT.3, I2C_BUS.3
I2C_SDA0: I2C-IN.2, I2C-OUT.2, SDA_SEL.1
I2C_SDA1: I2C-IN.4, I2C-OUT.4, SDA_SEL.3
MCP_A0: A0.2, R4.2, U2.15 (A0)
MCP_A1: A1.2, R5.2, U2.16 (A1)
MCP_A2: A2.2, R6.2, U2.17 (A2)
unnamed: LED.C, R1.1
SCL: I2C-BARE.3, I2C_BUS.2, R3.1, U2.12 (SCL)
SDA: I2C-BARE.4, R2.1, SDA_SEL.2, U2.13 (SDA)
VCC: A0.1, A1.1, A2.1, I2C-IN.9, I2C-OUT.9, LED.A, R2.2, R3.2, U2.9 (VDD)

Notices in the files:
parts and their libraries:
SparkFun-Connectors: Licensing: Creative Commons ShareAlike 4.0 International - https://creativecommons.org/licenses/by-sa/4.0
microbuilder: This work is placed in the public domain, and may be freely used for commercial and non-commercial work with the following conditions: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
